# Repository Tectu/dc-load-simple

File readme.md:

# Simple DC Dummy Load
A very simple DC dummy load.
PCB built using KiCAD.

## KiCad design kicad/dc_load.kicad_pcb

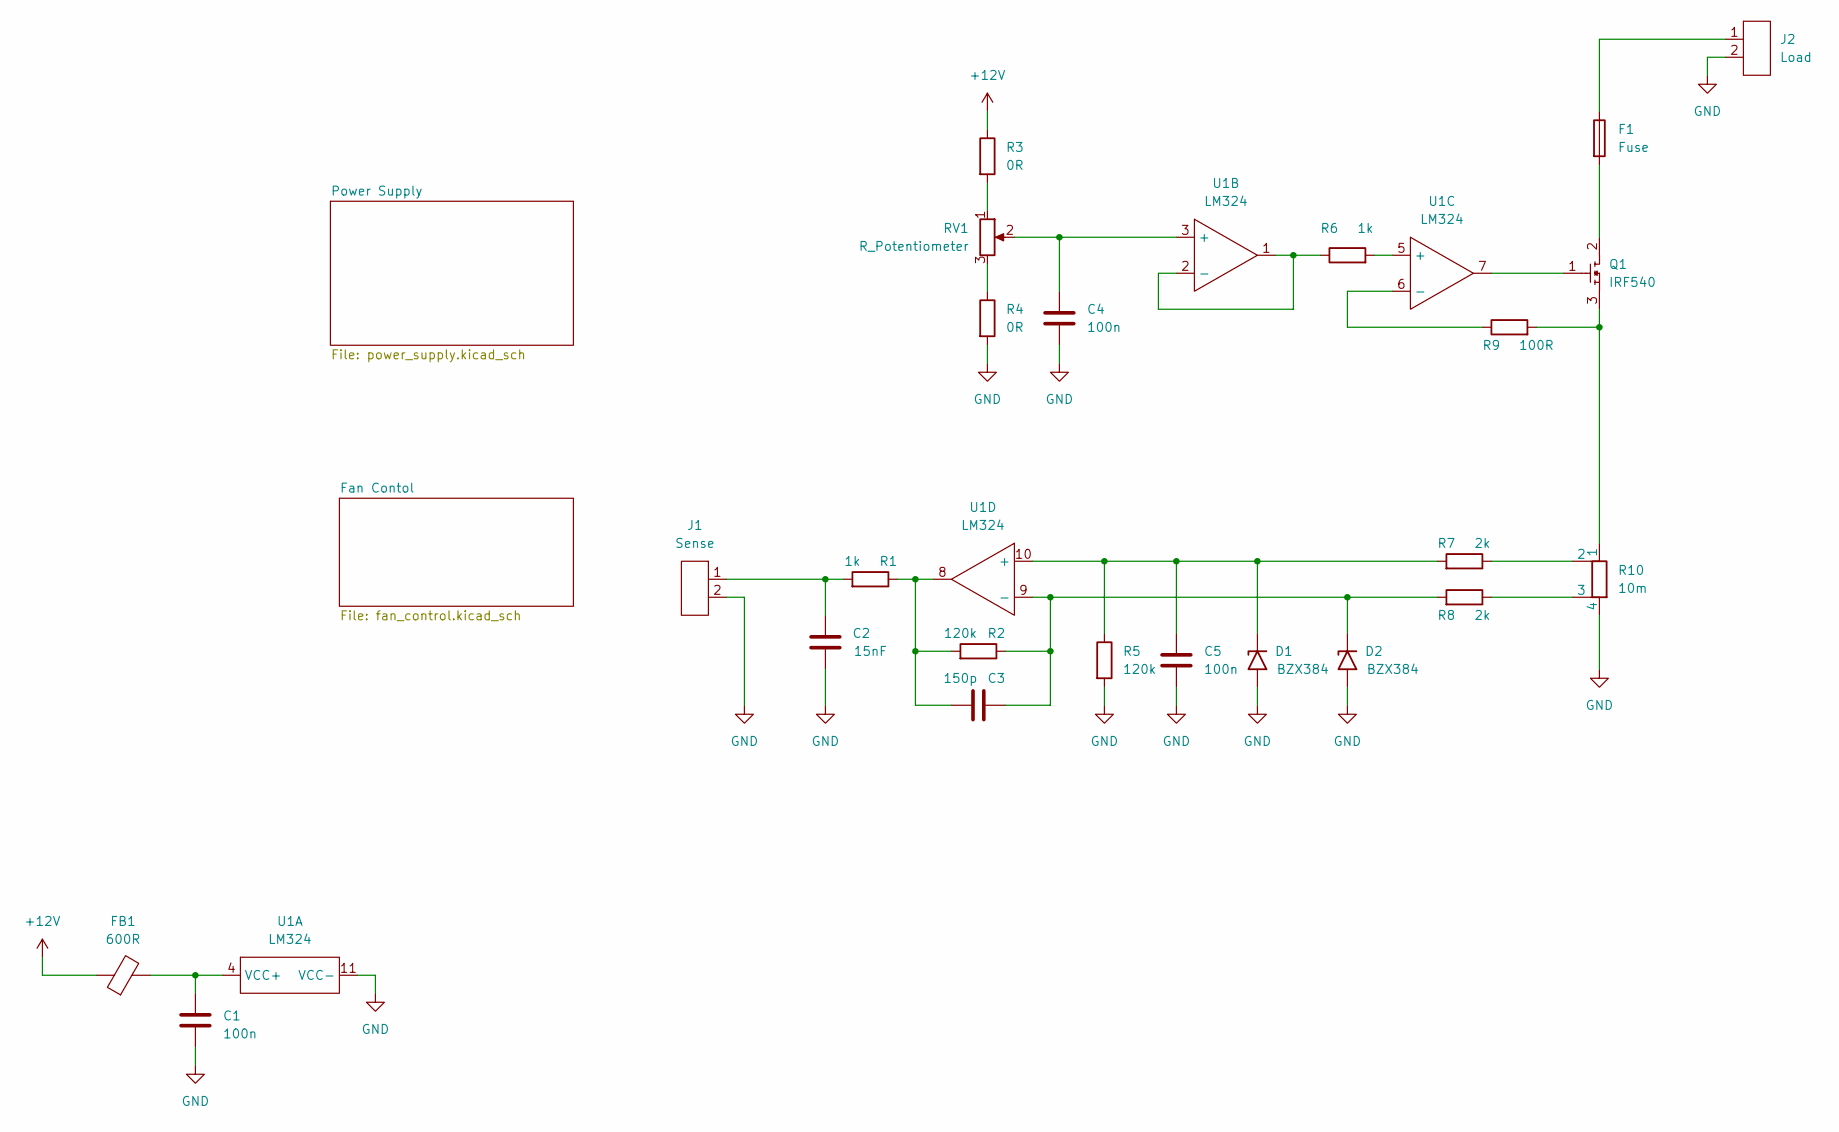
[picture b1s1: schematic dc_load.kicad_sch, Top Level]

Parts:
C1, C4, C5: 100n; C_0603_1608Metric
C2: 15nF; C_0603_1608Metric
C3: 150p; C_0603_1608Metric
D1, D2: BZX384; SOD-323
F1: Fuse; LittleFuse 178.6164.0000
FB1: 600R; ferrite_bead_0603
J1: Sense; molex_kk_1x2_horizontal_th
J2: Load; connector_phoenix
Q1: IRF540; TO-220 Horizontal Flipped
R1, R6: 1k; R_0603_1608Metric
R2, R5: 120k; R_0603_1608Metric
R3, R4: 0R; R_0603_1608Metric
R7, R8: 2k; R_0603_1608Metric
R9: 100R; R_0603_1608Metric
R10: 10m; R_Shunt_Vishay_WSK2512_6332Metric_T2.21mm
RV1: R_Potentiometer; Bourns 3296P
U1: LM324; SOIC-14

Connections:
+12V: FB1.1, R3.1; also elsewhere on the board
GND: C1.2, C2.1, C4.2, C5.2, D1.2 (A), D2.2 (A), J1.2, J2.2, R4.2, R5.2, R10.4, U1.11 (VCC-); also elsewhere on the board
unnamed: C1.1, FB1.2, U1.4 (VCC+)
unnamed: C2.2, J1.1, R1.2
unnamed: C3.1, R1.1, R2.2, U1.8
unnamed: C3.2, D2.1 (K), R2.1, R8.2, U1.9 (-)
unnamed: C4.1, RV1.2, U1.3 (+)
unnamed: C5.1, D1.1 (K), R5.1, R7.2, U1.10 (+)
unnamed: F1.1, J2.1
unnamed: F1.2, Q1.2
unnamed: Q1.1, U1.7
unnamed: Q1.3, R9.2, R10.1
unnamed: R3.2, RV1.1
unnamed: R4.1, RV1.3
unnamed: R6.1, U1.1, U1.2 (-)
unnamed: R6.2, U1.5 (+)
unnamed: R9.1, U1.6 (-)
unnamed: R7.1, R10.2
unnamed: R8.1, R10.3

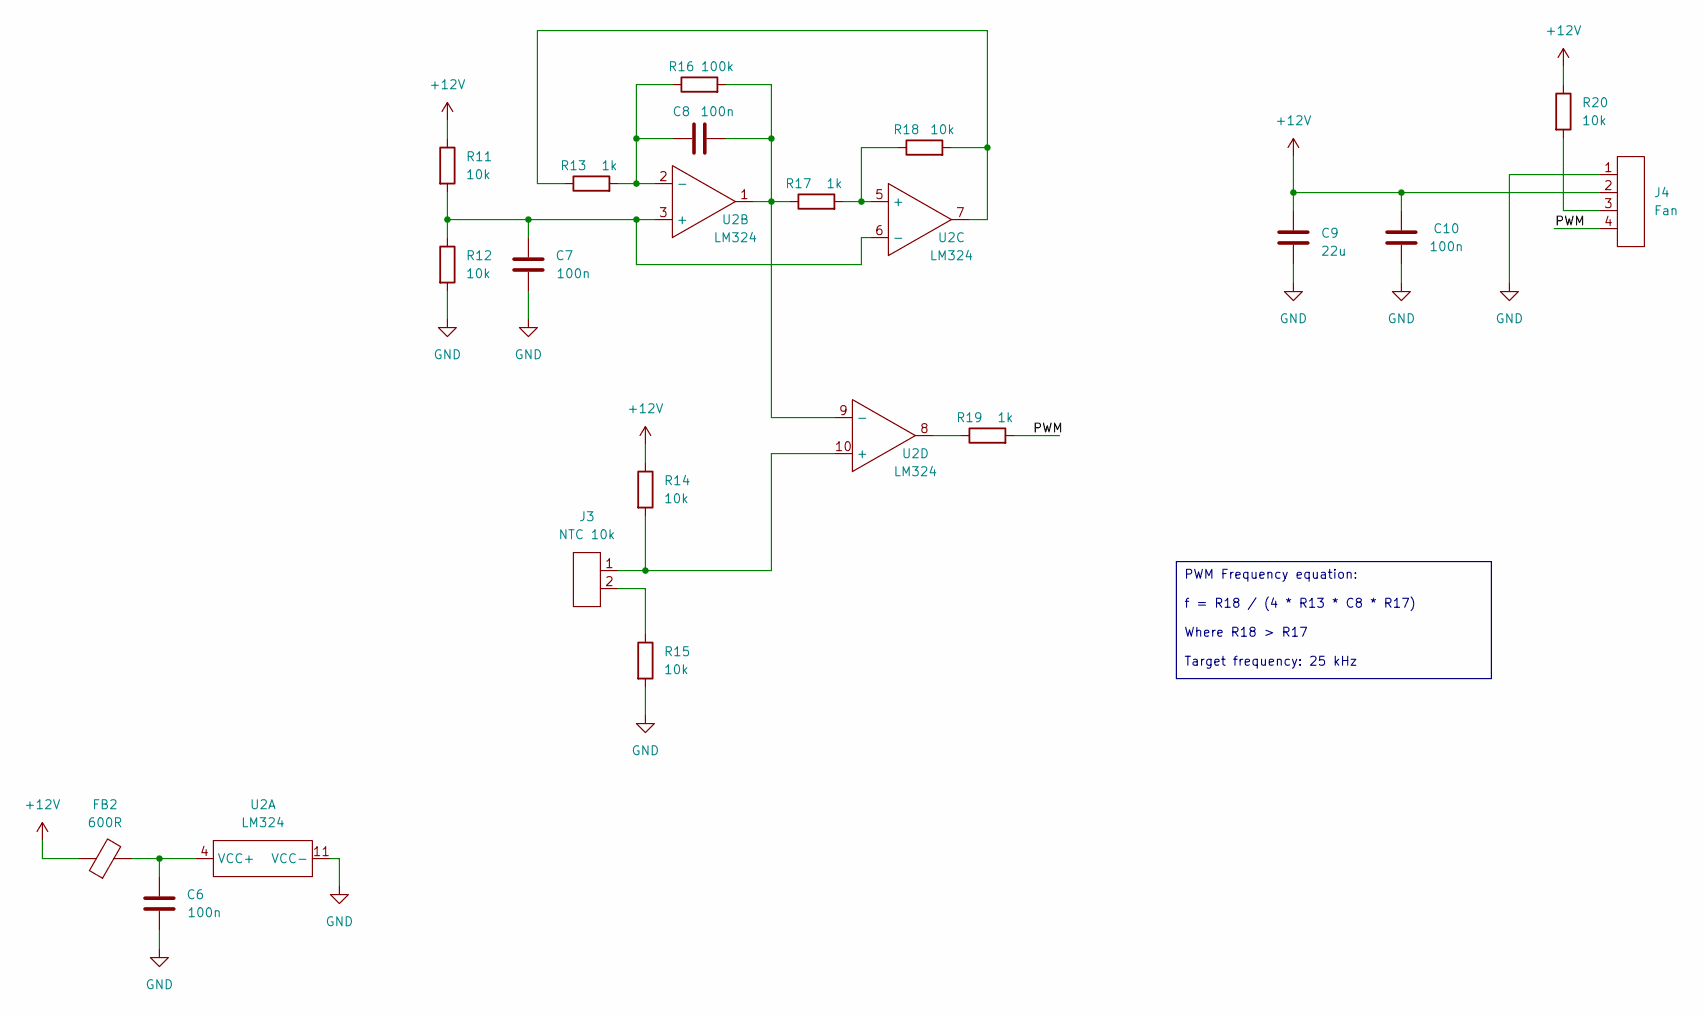
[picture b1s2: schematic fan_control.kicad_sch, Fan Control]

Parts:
C6, C7, C8, C10: 100n; C_0603_1608Metric
C9: 22u; CP_Elec_5x5.4
FB2: 600R; ferrite_bead_0603
J3: NTC 10k; molex_kk_1x2_vertical_th
J4: Fan; molex_kk_1x4_vertical_th
R11, R12, R14, R15, R18, R20: 10k; R_0603_1608Metric
R13, R17, R19: 1k; R_0603_1608Metric
R16: 100k; R_0603_1608Metric
U2: LM324; SOIC-14

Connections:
+12V: C9.1, C10.2, FB2.1, J4.2, R11.1, R14.1, R20.1; also elsewhere on the board
/Fan Contol/PWM: J4.4, R19.2
GND: C6.1, C7.1, C9.2, C10.1, J4.1, R12.2, R15.2, U2.11 (VCC-); also elsewhere on the board
unnamed: C6.2, FB2.2, U2.4 (VCC+)
unnamed: C7.2, R11.2, R12.1, U2.3 (+), U2.6 (-)
unnamed: C8.1, R13.2, R16.1, U2.2 (-)
unnamed: C8.2, R16.2, R17.1, U2.1, U2.9 (-)
unnamed: J3.1, R14.2, U2.10 (+)
unnamed: J3.2, R15.1
unnamed: J4.3, R20.2
unnamed: R13.1, R18.2, U2.7
unnamed: R17.2, R18.1, U2.5 (+)
unnamed: R19.1, U2.8

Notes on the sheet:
PWM Frequency equation: f = R18 / (4 * R13 * C8 * R17) Where R18 > R17 Target frequency: 25 kHz

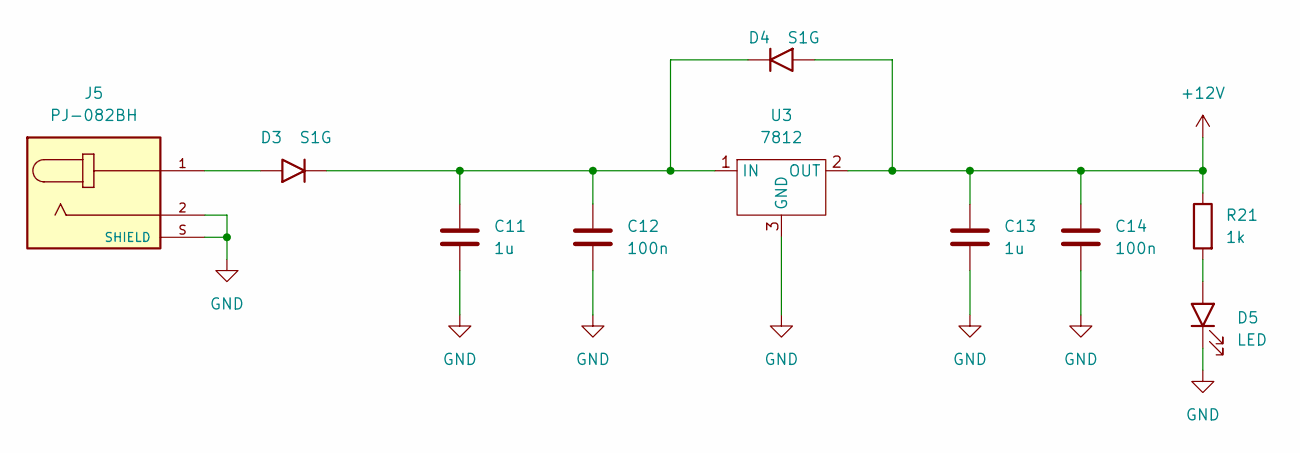
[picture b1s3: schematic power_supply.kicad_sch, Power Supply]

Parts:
C11, C13: 1u; CP_Elec_4x5.4
C12, C14: 100n; C_0603_1608Metric
D3, D4: S1G; DO-214AC
D5: LED; 0603
J5: PJ-082BH; PARTREV 1.0
R21: 1k; R_0603_1608Metric
U3: 7812; TO-252-3

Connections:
+12V: C13.1, C14.1, D4.2 (A), R21.1, U3.2 (OUT); also elsewhere on the board
GND: C11.2, C12.2, C13.2, C14.2, D5.1 (K), J5.2, J5.S (SHIELD), U3.3 (GND); also elsewhere on the board
unnamed: C11.1, C12.1, D3.1 (K), D4.1 (K), U3.1 (IN)
unnamed: D3.2 (A), J5.1
unnamed: D5.2 (A), R21.2

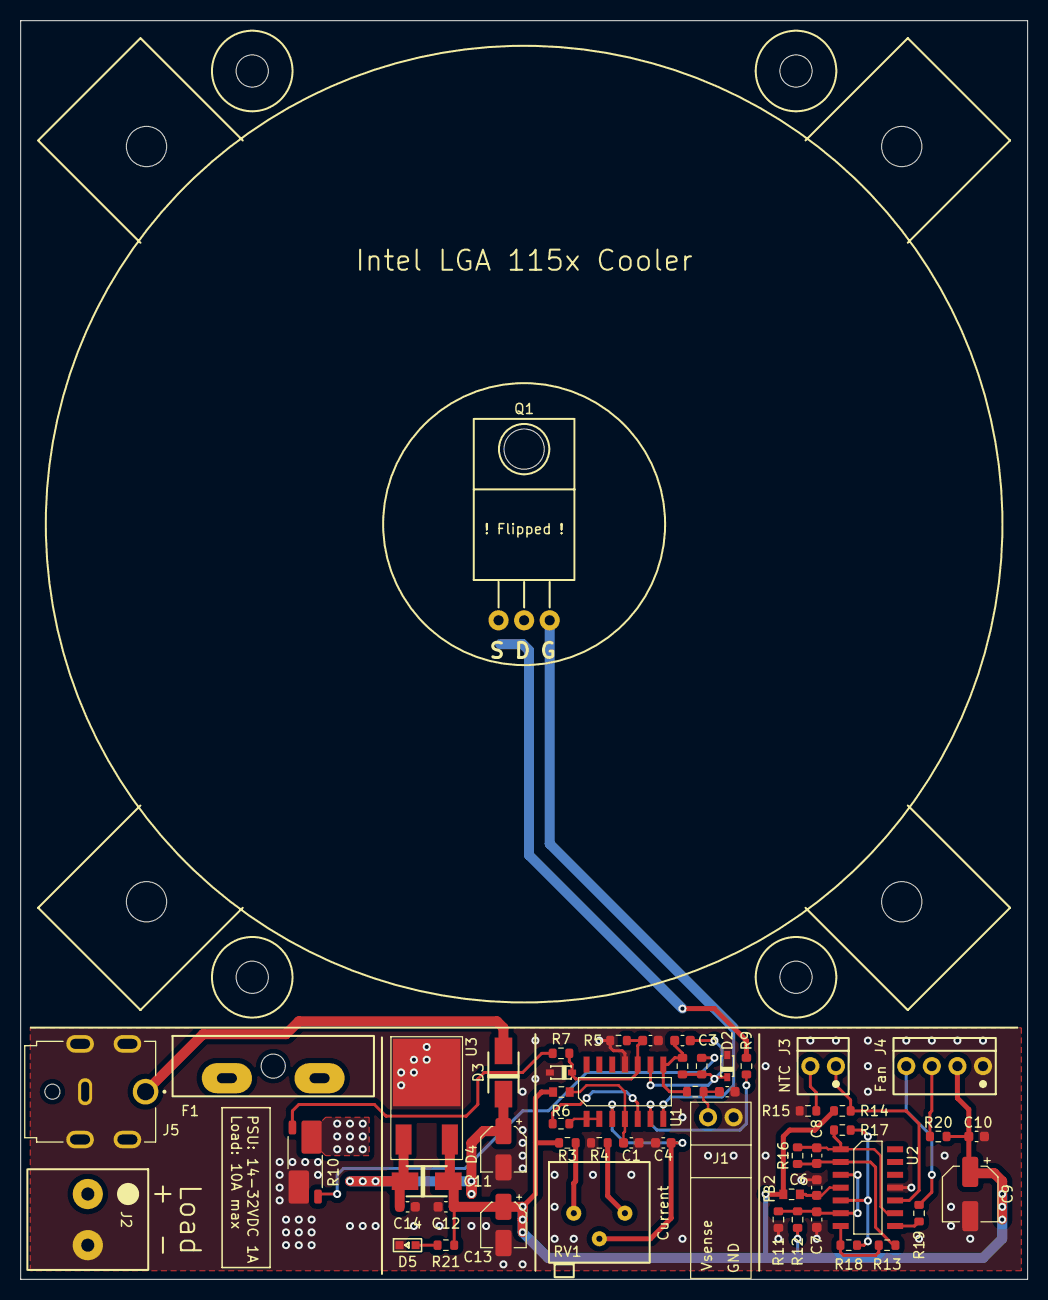
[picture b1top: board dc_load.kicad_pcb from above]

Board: 2 copper layers, 100.0 x 125.0 mm, 53 parts (0 on the bottom side), 33 nets.

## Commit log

2023-03-15 release v1.0
